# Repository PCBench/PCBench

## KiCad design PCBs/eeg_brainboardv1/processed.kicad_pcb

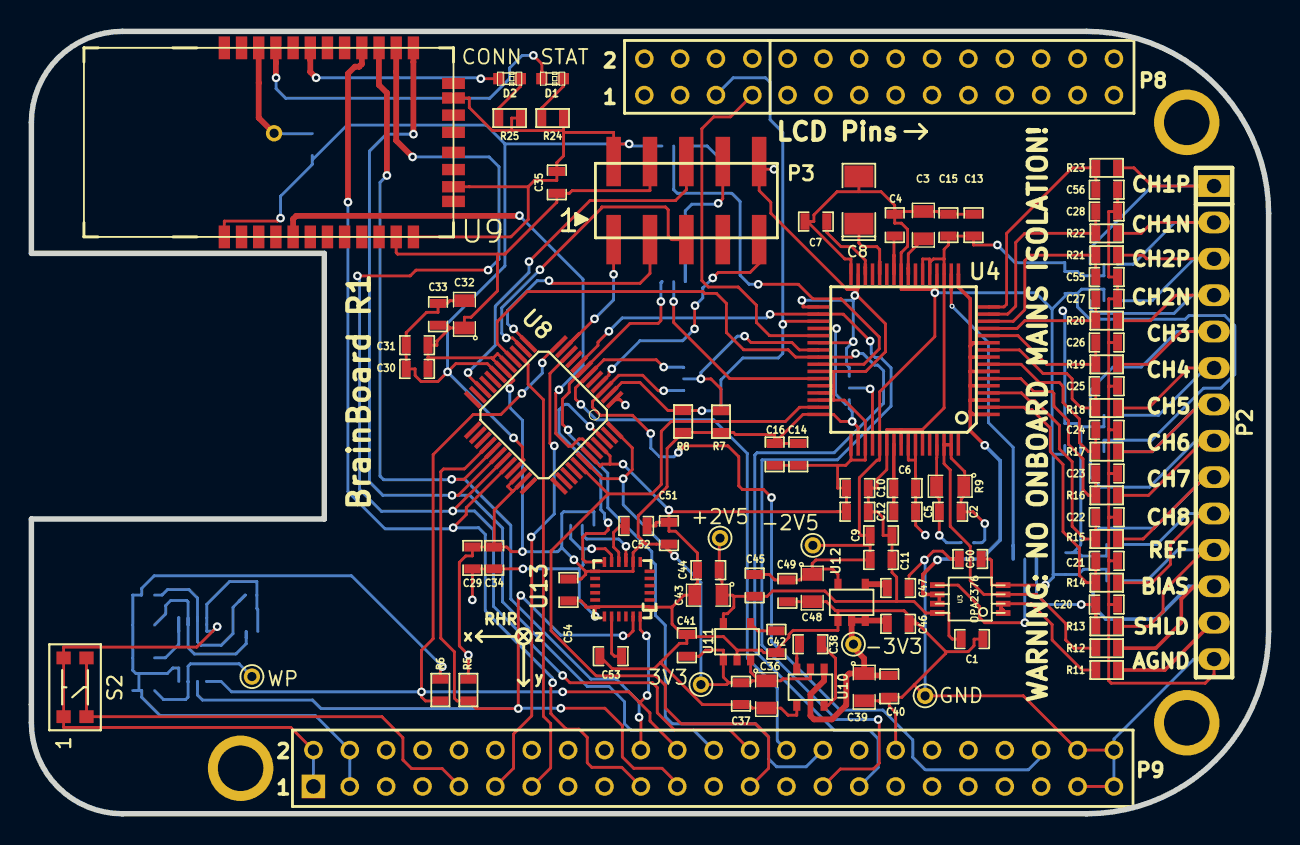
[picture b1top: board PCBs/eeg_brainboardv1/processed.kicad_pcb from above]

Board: 4 copper layers, 86.4 x 54.6 mm, 116 parts (0 on the bottom side), 86 nets.

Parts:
C1, C6, C11, C12, C15, C16, C17, C18, C19, C29, C31, C33, C34, C35, C45, C50, C51, C52: 0.1uF; SM0603_Capa
C2: 1nF; SM0603_Capa
C3, C32, C36, C39, C43, C48: 10uF; SM0805
C4, C5, C7, C9, C10, C13, C14, C37, C38, C40, C41, C46: 1uF; SM0603_Capa
C8: 100uF; SM1206POL
C20, C21, C22, C23, C24, C25, C26, C27, C28, C55, C56: 4.7nF; SM0603_Capa
C30, C44, C49: 2.2uF; SM0603_Capa
C42, C47, C54: 0.01uF; SM0603_Capa
C53: 2.2nF; SM0603_Capa
D1: STAT; LED-0603
D2: CONN; LED-0603
P1: WP; PINTST
P2: CONN_14; pin_strip_14
P3: CONN_5X2; bb02-hp10
P4: BTRST; PINTST
P5: GND; PINTST
P6: -3V3; PINTST
P7: 3V3; PINTST
P8: +2V5; PINTST
P9: -2V5; PINTST
P10: CONN_2X2; bb02-hp04
R1, R2, R3: 4.7K; SM0603
R4, R7, R8, R26: 10K; SM0603
R5, R6: 5.6K; SM0603
R9: 499K,0.1%; SM0805
R11, R12, R13, R14, R15, R16, R17, R18, R19, R20, R21, R22, R23: 4.99K; SM0603
R24, R25: 330; SM0603
S2: SMT_BUTTON; KMR231GLFS
SJ1: REF-SRB2; SparkFun-Passives-SJ_3_PASTE2&3
SJ2, SJ7: DAISY_CS; SparkFun-Passives-SJ_3_PASTE2&3
SJ3: NO BIAS FILT; SparkFun-Passives-SJ_2S-NO
SJ4: A2; SparkFun-Passives-SJ_2S-NOTRACE
SJ5: A1; SparkFun-Passives-SJ_2S-NOTRACE
SJ6: DAISY_OUT; SparkFun-Passives-SJ_3_PASTE2&3
SJ8: CLKSEL; SparkFun-Passives-SJ_3_PASTE1&2
SJ9: I2C Address Select (2&3NC); SparkFun-Passives-SJ_3_PASTE2&3
U1: 24C256; SSOP8
U2: BEAGLEBONE_BLACK; BEAGLEBONE_BLACK_EEGMOD
U3: OPA2376; msoic-8
U4: ADS1299; TQFP_64
U5, U6, U7: TPD4E001DBV; SOT23_6
U8: ATUC3L064; -TQFP48
U9: BLUETOOTH-RN42; SparkFun-RF-RN41
U10: TPS60403; SOT23-5
U11: TPS73225; SOT23-5
U12: TPS72325; SOT23-5
U13: MPU6050; QFN24-4x4

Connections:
+2.5V: C1.1, C9.1, C10.1, C11.1, C12.1, C13.1, C15.1, C17.1, C18.1, C19.1, C43.1, C44.1, C45.1, P8.1, U3.8, U4.19, U4.21, U4.22, U4.54, U4.56, U4.59, U5.5, U6.5, U7.5, U11.5
+3.3V: C14.1, C16.1, C29.1, C30.1, C31.1, C32.1, C33.1, C34.1, C35.1, C36.1, C37.1, C41.1, C51.1, C54.1, P3.4, P7.1, R1.1, R2.1, R3.1, R4.1, R5.1, R6.1, R7.1, R8.1, SJ8.1, SJ9.1, U1.8, U2.B3, U2.B4, U4.36, U4.48, U4.50, U8.17, U8.18, U8.34, U8.35, U8.42, U8.48, U9.11, U10.2, U11.1, U11.3, U13.8, U13.13
-2.5V: C3.1, C4.2, C5.2, C6.2, C7.2, C8.2, C9.2, C11.2, C13.2, C15.2, C17.2, C18.2, C19.2, C45.2, C48.1, C49.1, C50.1, P9.1, U3.4, U4.20, U4.23, U4.25, U4.32, U4.53, U4.57, U4.58, U5.2, U6.2, U7.2, U12.5
-3.3V: C39.1, C40.1, C46.1, P6.1, U10.1, U12.2, U12.3
/A0: R3.2, U1.1
/A1: R2.2, SJ5.1, U1.2
/A2: R1.2, SJ4.1, U1.3
/BrainBoard AFE//CS: R7.2, SJ2.2, U4.39
/BrainBoard AFE/BIASINV: C2.1, R9.2, SJ3.1, U4.61
/BrainBoard AFE/CLKSEL: SJ8.2, U4.52
/BrainBoard AFE/DAISY: SJ7.2, U4.41
/BrainBoard AFE/DAISY_IN: P10.1, SJ7.1
/BrainBoard AFE/DOUT: SJ6.2, U4.43
/BrainBoard AFE/SRB1: U3.6, U3.7, U4.1, U4.3, U4.5, U4.7, U4.9, U4.11, U4.17
/BrainBoard AFE/SRB2: SJ1.1, U4.18
/BrainBoard AFE/VCAP1: C8.1, U4.28
/BrainBoard AFE/VCAP2: C7.1, U4.30
/BrainBoard AFE/VCAP3: C5.1, C6.1, U4.55
/BrainBoard AFE/VCAP4: C4.1, U4.26
/BrainBoard AFE/VREFP: C3.2, U4.24
/BrainBoard Analog In/BIAS_ELEC: P2.12, R12.1, U7.3
/BrainBoard Analog In/BIAS_SHD: P2.13, R11.1
/BrainBoard Analog In/CH1ELEC_N: P2.2, R22.1, U5.6
/BrainBoard Analog In/CH1ELEC_P: P2.1, R23.1, U5.4
/BrainBoard Analog In/CH2ELEC_N: P2.4, R20.1, U5.3
/BrainBoard Analog In/CH2ELEC_P: P2.3, R21.1, U5.1
/BrainBoard Analog In/CH3ELEC_P: P2.5, R19.1, U6.4
/BrainBoard Analog In/CH4ELEC_P: P2.6, R18.1, U6.6
/BrainBoard Analog In/CH5ELEC_P: P2.7, R17.1, U6.1
/BrainBoard Analog In/CH6ELEC_P: P2.8, R16.1, U6.3
/BrainBoard Analog In/CH7ELEC_P: P2.9, R15.1, U7.4
/BrainBoard Analog In/CH8ELEC_P: P2.10, R14.1, U7.6
/BrainBoard Analog In/REF_ELEC: P2.11, R13.1, U7.1
/BrainBoard Bluetooth/FACTORY: P4.1, R26.1, U9.22
/BrainBoard Bluetooth/STATUS: D2.1, U9.19
/BrainBoard Bluetooth/STATUSn: D1.1, U9.21
/BrainBoard IMU/AD0: SJ9.2, U13.9
/BrainBoard IMU/CPOUT: C53.1, U13.20
/BrainBoard IMU/REGOUT: C52.1, U13.10
/BrainBoard MCU/RESET_MCU: P3.6, U8.22
/BrainBoard MCU/TCK: P3.1, U8.11
/BrainBoard MCU/TDI: P3.9, U8.4
/BrainBoard MCU/TDO: P3.3, U8.13
/BrainBoard MCU/TMS: P3.5, U8.14
/CS_DAISY: SJ2.1, U2.B42, U8.3
/CS_MAIN: SJ2.3, U2.B28, U8.6
/DRDY: U2.B25, U4.47, U8.41
/PWDN: R8.2, U2.A23, U4.35, U8.2
/WP: P1.1, R4.2, U1.7
AGND: C1.2, C10.2, C12.2, C14.2, C16.2, C20.2, C21.2, C22.2, C23.2, C24.2, C25.2, C26.2, C27.2, C28.2, C29.2, C30.2, C31.2, C32.2, C33.2, C34.2, C35.2, C36.2, C37.2, C39.2, C40.2, C41.2, C42.2, C43.2, C44.2, C46.2, C47.2, C48.2, C49.2, C50.2, C51.2, C52.2, C53.2, C54.2, C55.2, C56.2, P2.14, P3.2, P3.10, P5.1, R24.2, R25.2, R26.2, S2.1, S2.3, SJ4.2, SJ5.2, SJ7.3, SJ8.3, SJ9.3, U1.4, U2.B1, U2.B2, U2.B34, U2.B43, U2.B44, U2.B45, U2.B46, U4.31, U4.33, U4.38, U4.42, U4.44, U4.45, U4.46, U4.49, U4.51, U8.1, U8.19, U8.33, U8.43, U8.45, U9.1, U9.12, U9.28, U9.29, U10.4, U11.2, U12.1, U13.1, U13.11, U13.18
AIN1N: C28.1, R22.2, U4.15
AIN1P: C56.1, R23.2, U4.16
AIN2N: C27.1, R20.2, U4.13
AIN2P: C55.1, R21.2, U4.14
AIN3P: C26.1, R19.2, U4.12
AIN4P: C25.1, R18.2, U4.10
AIN5P: C24.1, R17.2, U4.8
AIN6P: C23.1, R16.2, U4.6
AIN7P: C22.1, R15.2, U4.4
AIN8P: C21.1, R14.2, U4.2
BIAS: C2.2, R9.1, R12.2, SJ3.2, U3.3, U4.62, U4.63
CLK: U2.A25, U4.37
DAISY_OUT: P3.8, SJ6.1
I2C2_SCL: R5.2, U1.6, U2.B21, U8.28, U13.23
I2C2_SDA: R6.2, U1.5, U2.B22, U8.12, U13.24
IMU_INT: U8.46, U13.12
MISO: SJ6.3, U2.B30, U8.7
MOSI: U2.B29, U4.34, U8.8
unnamed: S2.2, S2.4, U2.B9
unnamed: D2.2, R25.1
unnamed: D1.2, R24.1
unnamed: C47.1, U12.4
unnamed: C38.1, U10.5
unnamed: C38.2, U10.3
unnamed: C42.1, U11.4
unnamed: SJ1.2, U3.5
REF: C20.1, R13.2, SJ1.3
RESET_BT: U8.44, U9.5
SCLK: U2.B31, U4.40, U8.16
SHIELD: R11.2, U3.1, U3.2
UARTBT_CTS: U2.B20, U8.29, U9.15
UARTBT_RTS: U2.B19, U8.32, U9.16
UARTBT_RX: U2.B26, U8.31, U9.14
UARTBT_TX: U2.B24, U8.30, U9.13
UARTUC_RX: U2.B13, U8.15
UARTUC_TX: U2.B11, U8.10

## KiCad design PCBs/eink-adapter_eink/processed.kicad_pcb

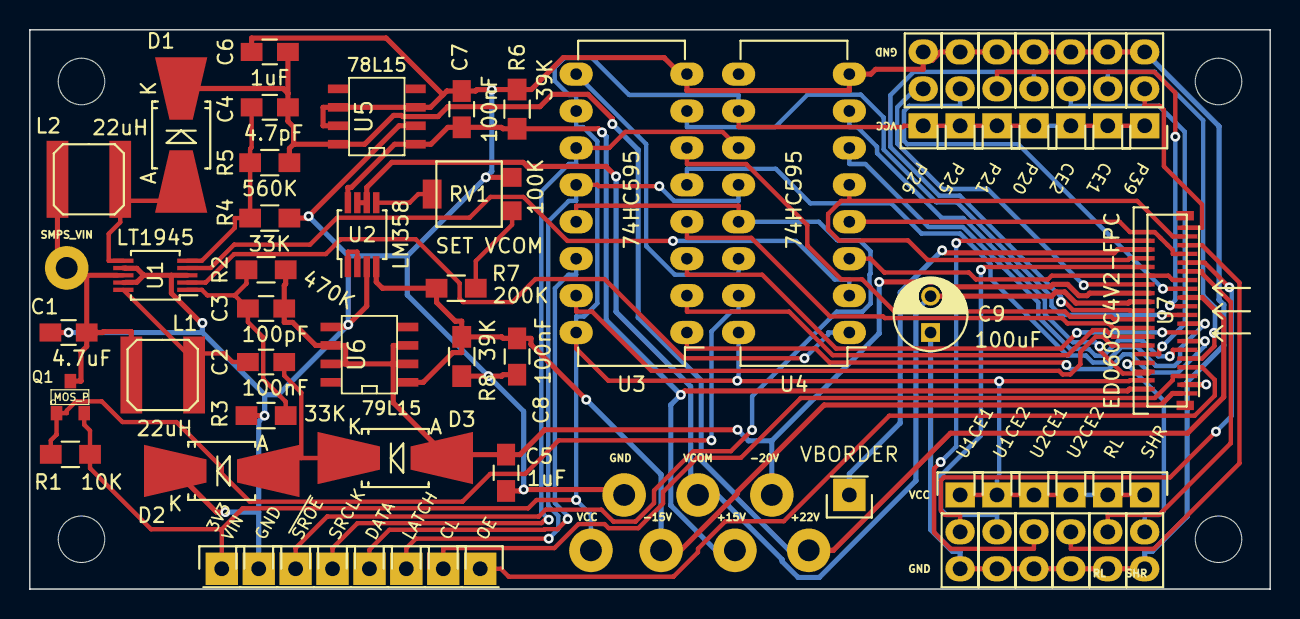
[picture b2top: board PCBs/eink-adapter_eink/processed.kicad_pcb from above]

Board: 2 copper layers, 85.3 x 38.5 mm, 65 parts (0 on the bottom side), 53 nets.

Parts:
C1: 4.7uF; C_0805_HandSoldering
C2, C7, C8: 100nF; C_0805_HandSoldering
C3: 100pF; C_0805_HandSoldering
C4: 4.7pF; C_0805_HandSoldering
C5, C6: 1uF; C_0805_HandSoldering
C9: 100uF; C_Radial_D5_L6_P2.5
D1, D2, D3: D_Schottky; SMB-SMC_Universal_Handsoldering
L1, L2: 22uH; SELF-WE-TPC_M
MNT1, MNT2, MNT3, MNT4: MountingHole_3.2mm_M3
P1, P7, P8, P9: CONN_1; Pin_Header_Straight_1x01
P2, P3, P5, P6, P10: CONN_01X01; Pin_Header_Straight_1x01
Q1: MOS_P; IRLML6402
R1: 10K; R_0805_HandSoldering
R2: 470K; R_0805_HandSoldering
R3, R4: 33K; R_0805_HandSoldering
R5: 560K; R_0805_HandSoldering
R6, R8: 39K; R_0805_HandSoldering
R7: 200K; R_0805_HandSoldering
RV1: 100K; Bourns_3314G-1
SW1, SW2, SW3, SW4, SW5, SW6, SW7, SW8, SW9, SW10, SW11, SW12, SW13: SW_SPDT_Small; Pin_Header_Straight_1x03
U1: LT1945; MSOP-10_3x3mm_Pitch0.5mm
U2: LM358; MSOP-8_3x3mm_Pitch0.65mm
U3, U4: 74HC595; DIP-16_W7.62mm_LongPads
U5: 78L15; 78LxxA
U6: 79L15; 79LxxA
U7: ED060SC4V2-FPC; FH26-39S-0.3SHW-biggerpads
W1, W2, W3, W4, W5, W6, W7, W8: TEST_1P; Measurement_Point_Round-TH_Big

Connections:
/+15V: C7.1, R6.1, U2.8, U5.VO, U7.2, W5.1
/+22V: C4.1, C6.2, D1.1, R5.2, U5.VI, U7.23, W7.1
/-15V: C8.1, R7.2, R8.1, U2.4, U6.VO, U7.1, W4.1
/-20V: C3.1, C5.1, D3.2, R2.1, U6.VI, U7.24, W8.1
/CE1: SW2.2, U7.9
/CE2: SW3.2, U7.10
/CKV: U4.4, U7.33, U7.38
/CL: P7.1, U7.5
/D0: U3.15, U7.12
/D1: U3.1, U7.13
/D2: U3.2, U7.14
/D3: U3.3, U7.15
/D4: U3.4, U7.16
/D5: U3.5, U7.17
/D6: U3.6, U7.18
/D7: U3.7, U7.19
/FB2: C4.2, R4.2, R5.1, U1.5
/GMODE: U4.3, U7.27, U7.28
/LATCH: P5.1, U3.12, U4.12
/LE: U4.7, U7.6
/NFB1: C3.2, R2.2, R3.1, U1.1
/OE: P8.1, U7.7
/P20: SW4.2, U7.20
/P21: SW5.2, U7.21
/P25: SW6.2, U7.25
/P26: SW7.2, U7.26
/P39: SW13.2, U7.39
/RL: SW8.2, U7.29
/SHR: SW1.2, U7.8
/SMPS_CTRL: Q1.G, R1.2, U4.15
/SMPS_VIN: C1.1, L1.1, L2.1, Q1.D, U1.8, W1.1
/SPH: U4.6, U7.11
/SPV: U4.5, U7.32, U7.37
/SRCLK: P3.1, U3.11, U4.11
/SRDATA: P2.1, U3.14
/SW1: C2.1, L1.2, U1.10
/SW2: D1.2, L2.2, U1.6
/U1CE1: SW10.2, U7.31
/U1CE2: SW9.2, U7.30
/U2CE1: SW12.2, U7.36
/U2CE2: SW11.2, U7.35
/VBORDER: P9.1, U7.34
/VCOM: C9.2, U2.6, U2.7, U7.22, W6.1
/VNEG_CTRL: U1.2, U4.1
/VPOS_CTRL: U1.4, U4.2
/~SROE~: P6.1, U3.13, U4.13
GND: C1.2, C5.2, C6.1, C7.2, C8.2, C9.1, D2.1, P1.1, R3.2, R4.1, R6.2, R8.2, RV1.1, SW1.3, SW2.3, SW3.3, SW4.3, SW5.3, SW6.3, SW7.3, SW8.3, SW9.3, SW10.3, SW11.3, SW12.3, SW13.3, U1.3, U1.7, U1.9, U2.3, U3.8, U4.8, U5.GND, U6.GND, U7.3, W2.1
unnamed: C2.2, D2.2, D3.1
unnamed: R7.1, RV1.3
unnamed: RV1.2, U2.5
unnamed: U2.1, U2.2
unnamed: U3.9, U4.14
VCC: P10.1, Q1.S, R1.1, SW1.1, SW2.1, SW3.1, SW4.1, SW5.1, SW6.1, SW7.1, SW8.1, SW9.1, SW10.1, SW11.1, SW12.1, SW13.1, U3.10, U3.16, U4.10, U4.16, U7.4, W3.1

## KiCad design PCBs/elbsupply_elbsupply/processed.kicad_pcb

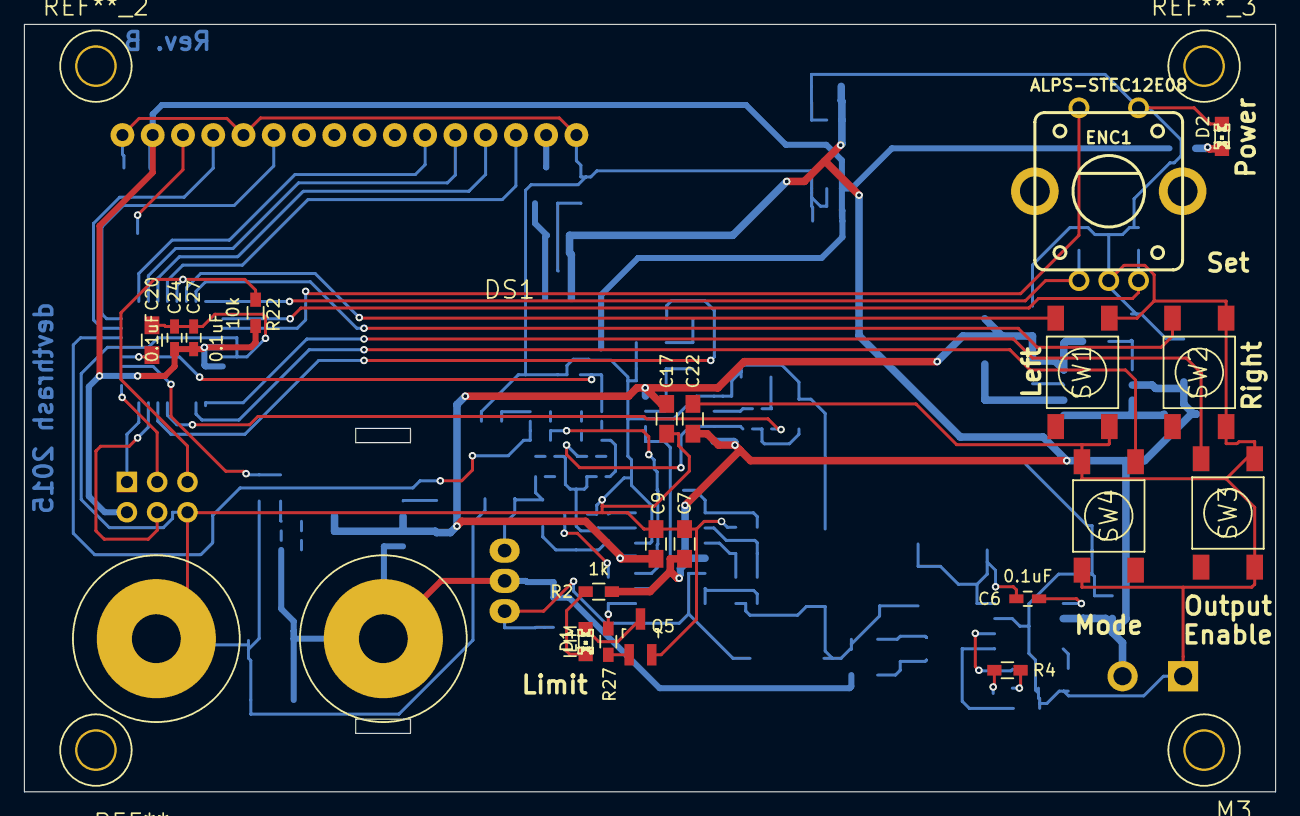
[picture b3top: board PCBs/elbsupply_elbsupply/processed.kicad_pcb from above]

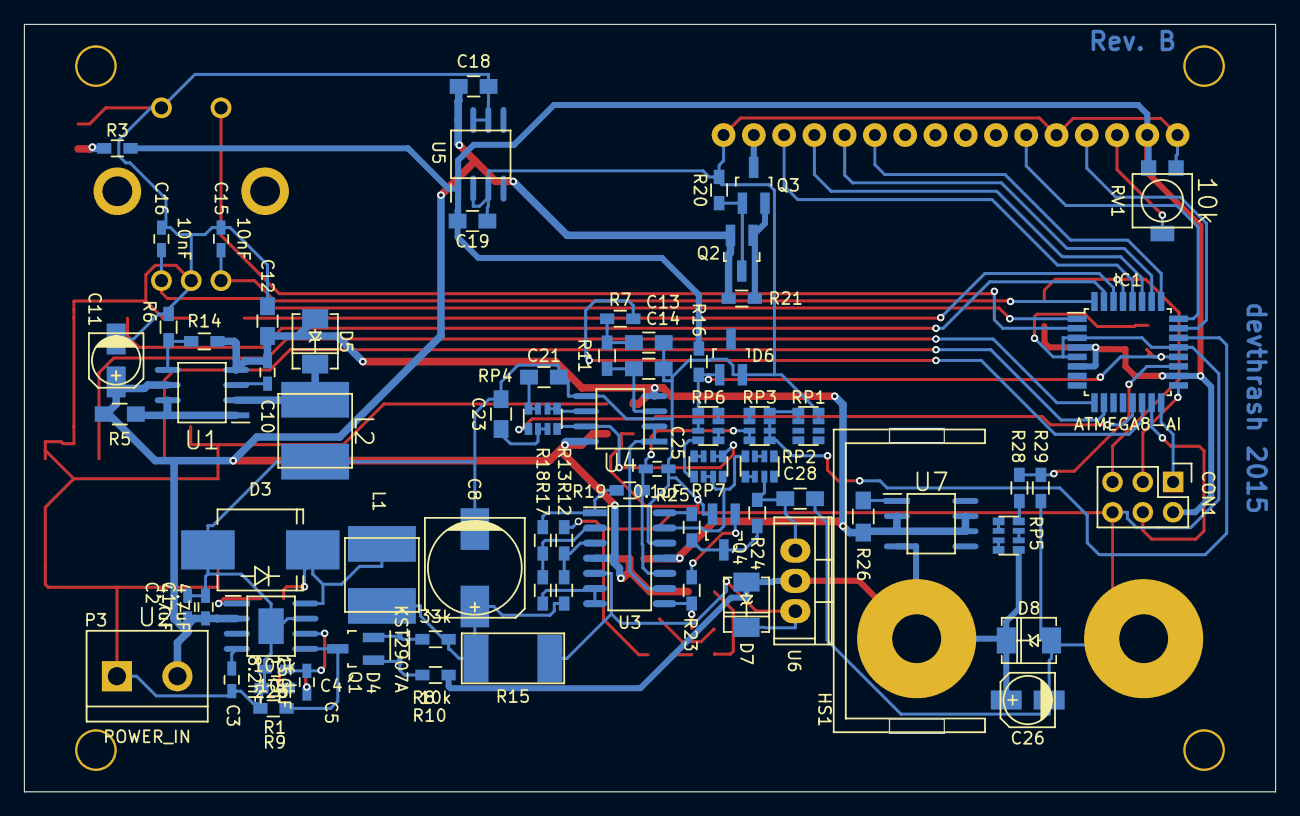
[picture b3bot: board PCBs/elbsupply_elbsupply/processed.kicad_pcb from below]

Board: 2 copper layers, 105.0 x 64.4 mm, 100 parts (76 on the bottom side), 82 nets.

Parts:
C1, C2: 4.7uF; C_0603_HandSoldering
C3: 8.2nF; C_0603_HandSoldering
C4: 22pF; C_0603_HandSoldering
C5: 150pF; C_0603_HandSoldering
C6, C24, C25, C27: 0.1uF; C_0603_HandSoldering
C7, C9, C17, C22: 0.1uF; C_0805_HandSoldering
C8: 220uF; c_elec_8x10.5
C10: 120pF; C_0603_HandSoldering
C11, C26: 10uF; c_elec_4x4.5
C12: 10uF; C_0805_HandSoldering
C13, C14, C18, C19, C20, C21, C23, C28: 1uF; C_0805_HandSoldering
C15, C16: 10nF; C_0603_HandSoldering
CON1: AVR-ISP-6; Pin_Header_Straight_2x03
D1: ILIM; LED-0805
D2: POWER; LED-0805
D3: SK54C; Diode-SMC_Handsoldering
D4: 1N4148WS; SOD-323
D5, D7, D8: SK34A; DO-214-AC_SMA
D6: LM4040; SOT-23_Handsoldering
DS1: LCD-016N002L; LCD16X2
ENC1: ALPS-STEC12E08
HS1: HEATSINK V5640A; Heatsink-V5640A
IC1: ATMEGA8-AI; TQFP-32_7x7mm_Pitch0.8mm
L1: 4,7uH; 242418FPS-Fastron
L2: 220uH; 242418FPS-Fastron
M3: Screw_PAN_Head_M3
P1: OUT_POS; SKS-PK10A
P2: OUT_GND; SKS-PK10A
P3: POWER_IN; bornier2
Q1: KST2907A; SOT23_Handsoldering
Q2: KST2907A; SOT-23_Handsoldering
Q3: IRLML6302; SOT-23_Handsoldering
Q4, Q5: 2N2222A; SOT-23_Handsoldering
R1, R13, R18: 100k; R_0603_HandSoldering
R2, R3, R20, R25: 1k; R_0603_HandSoldering
R4, R8: 33k; R_0603_HandSoldering
R5: 1R; R_0805_HandSoldering
R6: 18k; R_0603_HandSoldering
R7, R9, R10, R11, R12, R17, R19, R22, R23, R27, R28, R29: 10k; R_0603_HandSoldering
R14: 3k9; R_0603_HandSoldering
R15: 0R1; CRA2512-Bourns
R16: 220; R_0603_HandSoldering
R21: 10R; R_0603_HandSoldering
R24: 100; R_0603_HandSoldering
R26: 10R; R_0805_HandSoldering
RP1, RP2, RP3, RP4, RP5, RP6, RP7: 10k; YC164-Yageo-Handsoldering
RV1: 10k; BITech-23B
SW1: SW_L; Button-SMT-standard
SW2: SW_R; Button-SMT-standard
SW3: SW_OE; Button-SMT-standard
SW4: SW_MD; Button-SMT-standard
U1: MC34063; SO8
U2: TPS54331DDA; SO8-PowerPAD
U3: LM324; SO14
U4: LM358; SO8
U5: TS78L05CS; SO8
U6: LM350T; TO-220
U7: LM334; SO8

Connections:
+5V: C19.1, C24.2, C27.1, CON1.2, DS1.2, IC1.4, IC1.6, IC1.18, R3.1, R16.1, R22.2, RV1.1, U5.1
/2.5VREF: C20.1, D6.1, IC1.20, R16.2, RP6.1
/ENC_A: C15.1, ENC1.A, IC1.32
/ENC_B: C16.1, ENC1.B, IC1.1
/ENC_SW: ENC1.SW1, IC1.2
/ILIM: R23.1, R27.2, U3.8
/I_ADC: IC1.22, RP3.5, RP3.6, RP3.7
/I_Meas: C25.1, R19.1, RP3.3, RP3.4, U3.10
/I_PWM: IC1.14, R7.2
/I_Set: U3.9, U4.1, U4.2
/LCD_D4: DS1.11, IC1.25
/LCD_D5: DS1.12, IC1.26
/LCD_D6: DS1.13, IC1.27
/LCD_D7: DS1.14, IC1.28
/LCD_E: DS1.6, IC1.24
/LCD_RS: DS1.4, IC1.23
/LED_CC: DS1.15, Q3.3
/LED_CS: Q2.1, Q3.2, R21.2
/LIN_IN: D7.2, R15.1, U3.5, U6.3
/LIN_OUT: C26.1, D7.1, D8.2, P1.1, R10.2, RP5.1, U6.2, U7.4
/MC34_Coll: R5.1, U1.1, U1.7, U1.8
/MC34_Emit: D5.2, L2.1, U1.2
/MISO: CON1.1, IC1.16
/MOSI: CON1.4, IC1.15
/SCK: CON1.3, IC1.17
/SMPS_OUT: C8.1, L1.2, R8.1, R12.2, R15.2
/SMPS_SW: C6.2, D3.2, L1.1, U2.8
/SW_L: IC1.30, SW1.2
/SW_MD: IC1.10, SW4.2
/SW_OE: IC1.9, SW3.2
/SW_R: IC1.31, SW2.2
/V_ADC: IC1.19, R28.2, R29.2
/V_PWM: IC1.13, RP4.5
/V_Set: RP4.8, RP7.1, RP7.2, U4.7
/~RST~: CON1.5, IC1.29, R22.1
GND: C1.1, C2.1, C3.1, C4.1, C7.2, C8.2, C9.2, C11.2, C12.1, C13.2, C14.2, C15.2, C16.2, C17.2, C18.2, C19.2, C20.2, C21.2, C22.2, C23.2, C24.1, C25.2, C26.2, C27.2, C28.2, CON1.6, D2.1, D3.1, D6.2, D8.1, DS1.1, DS1.5, DS1.16, ENC1.C, ENC1.SW2, IC1.3, IC1.5, IC1.21, L2.2, P2.1, P3.1, Q4.2, Q5.2, R1.2, R6.2, R9.2, R13.1, R20.2, R29.1, RP1.3, RP1.4, RV1.3, SW1.1, SW2.1, SW3.1, SW4.1, U2.7, U2.9, U3.12, U4.5, U5.2, U5.3, U5.6, U5.7
unnamed: C3.2, U2.4
unnamed: C4.2, C5.1, U2.6
unnamed: C5.2, R4.1
unnamed: C6.1, U2.1
unnamed: C10.1, U1.3
unnamed: C13.1, R7.1, R11.2
unnamed: C14.1, R11.1, U4.3
unnamed: C21.1, RP4.3, RP4.4
unnamed: C23.1, RP4.6, RP4.7
unnamed: C28.1, R24.1, RP2.7, U6.1
unnamed: D1.1, Q5.3
unnamed: D1.2, R2.2
unnamed: D2.2, R3.2
unnamed: D4.1, Q1.1, R10.1
unnamed: D4.2, Q1.2, R8.2
unnamed: DS1.3, RV1.2
unnamed: Q1.3, R9.1, U2.5
unnamed: Q2.3, Q3.1, R20.1
unnamed: Q4.1, R23.2
unnamed: Q4.3, R24.2, R25.1
unnamed: Q5.1, R27.1
unnamed: R1.1, R4.2
unnamed: R12.1, R13.2, U3.3
unnamed: R6.1, R14.2, U1.5
unnamed: R17.1, U3.6, U3.7
unnamed: R17.2, R18.2, U3.2
unnamed: R18.1, R19.2, U3.1
unnamed: R25.2, U3.14
unnamed: R26.1, U7.1
unnamed: R28.1, RP5.4
unnamed: RP1.5, RP1.6, RP3.8
unnamed: RP2.2, RP2.3
unnamed: RP2.4, RP7.6, RP7.7, U3.13
unnamed: RP2.5, RP2.6
unnamed: RP3.1, RP3.2
unnamed: RP4.1, RP4.2, U4.6
unnamed: RP5.2, RP5.3
unnamed: RP5.5, RP5.6
unnamed: RP5.7, RP5.8
unnamed: RP6.2, RP6.3
unnamed: RP6.4, RP7.5
unnamed: RP6.5, RP6.6
unnamed: RP6.7, RP6.8
unnamed: RP7.3, RP7.4
VCC: C1.2, C2.2, C7.1, C11.1, C18.1, C22.1, P3.2, Q2.2, R2.1, R5.2, R21.1, U1.6, U2.2, U3.4, U4.8, U5.8
VEE: C9.1, C10.2, C12.2, C17.1, D5.1, R14.1, R26.2, U1.4, U3.11, U4.4, U7.2, U7.3, U7.6, U7.7

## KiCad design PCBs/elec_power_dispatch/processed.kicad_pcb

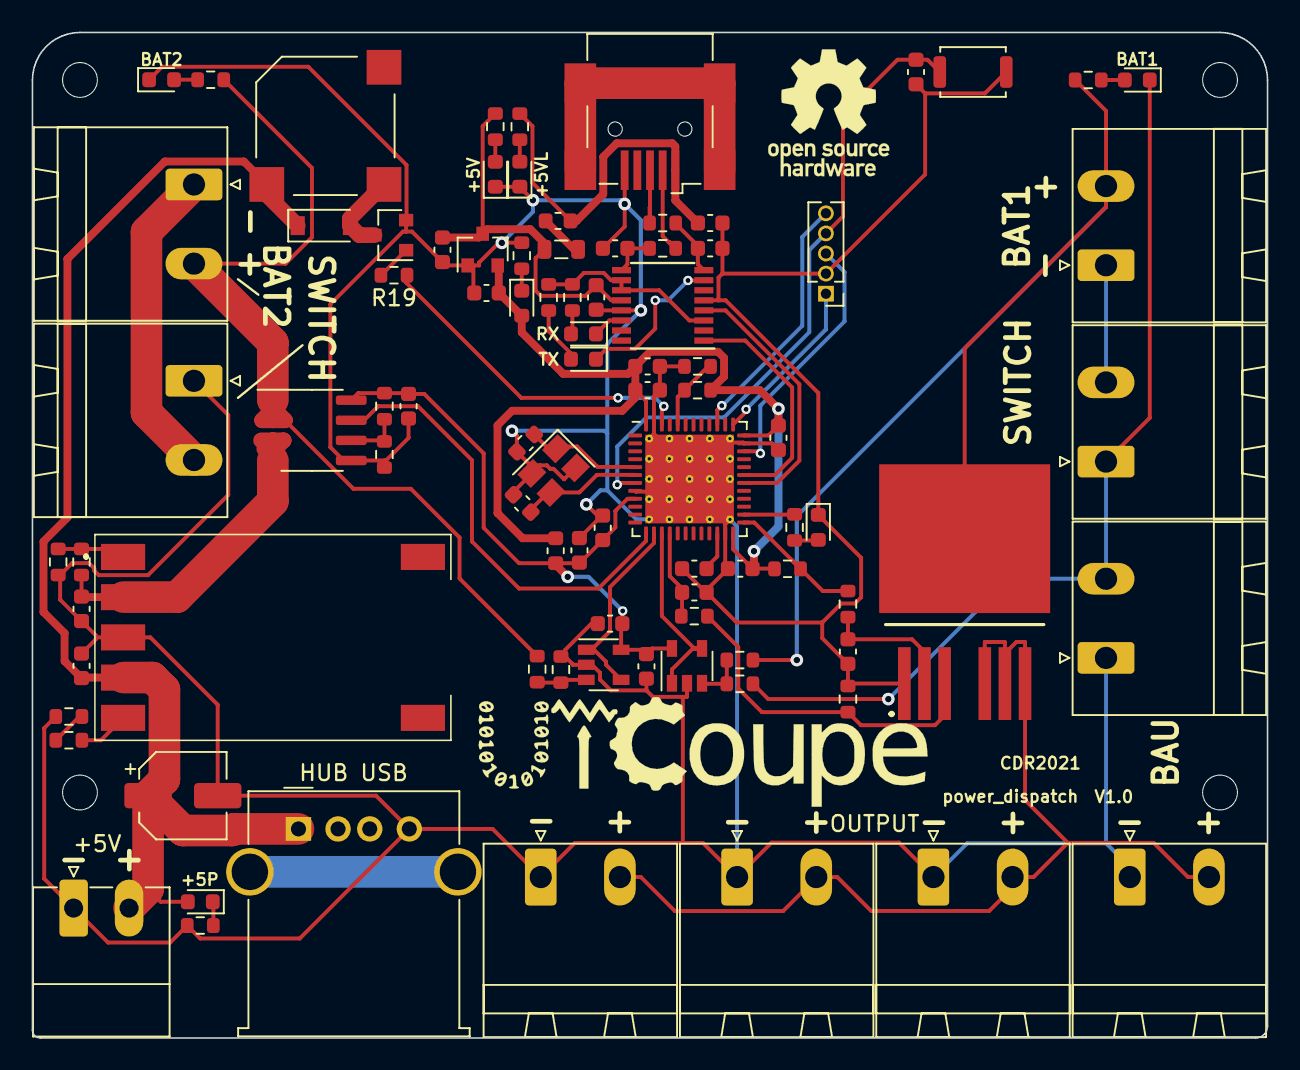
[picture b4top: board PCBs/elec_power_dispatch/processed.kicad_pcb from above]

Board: 2 copper layers, 78.0 x 63.5 mm, 95 parts (0 on the bottom side), 57 nets.

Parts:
BZ1: MLT-8530; MagneticBuzzer_Kobitone_254-EMB84Q-RO
C1, C4, C9, C13, C14, C15, C17, C18, C22, C24, C26: 100nF; C_0603_1608Metric
C2: 100uF/10V; CP_Elec_5x5.4
C3, C6, C12: 4u7; C_0603_1608Metric
C5, C7: 10uF; C_0603_1608Metric
C8: 220nF; C_0603_1608Metric
C10, C11: 12pF; C_0603_1608Metric
C16: 1u; C_0603_1608Metric
C19: 10nF; C_0603_1608Metric
C23, C25: 47pF; C_0603_1608Metric
D1, D2, D3, D4, D7, D9: red0603; LED_0603_1608Metric
D5, D6: blue0603; LED_0603_1608Metric
D8: 1N4148W; D_SOD-123
D10: green0603; LED_0603_1608Metric
F1: 100mA; Fuse_0603_1608Metric
FB1: 100 @ 100MHz; L_0805_2012Metric
H1, H2, H3, H4: MountingHole; MountingHole_2.2mm_M2
IC1: SRBH-06H1A1G; SRBH06H1A1G
IC2: BTS500251TADATMA2; IPB180N03S4L01
J1, J2, J3, J4, J5, J8, J9, J10, J11: Conn_01x02; PhoenixContact_MSTBA_2,5_2-G_1x02_P5.00mm_Horizontal
J6: USB_B_Mini; USB_Mini-B_Wuerth_65100516121_Horizontal
J7: Conn_01x05; PinHeader_1x05_P1.27mm_Vertical
J13: Conn_01x02; PhoenixContact_MC_1,5_2-G-3.5_1x02_P3.50mm_Horizontal
J15: USB_A; USB_A_Molex_67643_Horizontal
L1: 39nH; L_0603_1608Metric
LOGO1: Logo_Open_Hardware_Large; OSHW-Logo_7.5x8mm_SilkScreen
Q1: 2N7002E; SOT-23
R1, R10, R14, R24, R26: 3K3; R_0603_1608Metric
R2, R12: 4K7; R_0603_1608Metric
R3, R5, R6, R8, R25, R27, R28: 10K; R_0603_1608Metric
R4: 2K2; R_0603_1608Metric
R7, R9: 1K5; R_0603_1608Metric
R11, R13: 1K; R_0603_1608Metric
R15, R16: 27R; R_0603_1608Metric
R17, R20, R21: NC; R_0603_1608Metric
R18: 0R; R_0603_1608Metric
R19: 470R; R_0603_1608Metric
R22, R23: 270R; R_0603_1608Metric
SW1: SKRKAEE020; SW_Push_SPST_NO_Alps_SKRK
U1, U8: MCP6L01x-xOT; SOT-23-5
U2: STM32F411CEUx; QFN-48-1EP_7x7mm_P0.5mm_EP5.6x5.6mm_ThermalVias
U3: FT230XS; SSOP-16_3.9x4.9mm_P0.635mm
U4: ACS722xLCTR-10AB; SOIC-8_3.9x4.9mm_P1.27mm
U5: XC6206P332MR; SOT-23
Y1: 1C208000BC0K 8MHz; Crystal_SMD_3225-4Pin_3.2x2.5mm

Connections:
+3.3VA: C4.1, C9.1, C16.2, C17.2, C18.1, L1.2, R17.1, U1.5, U2.9, U4.8, U8.5
+3V3: C7.1, C12.2, C13.2, C14.2, C22.2, D7.2, L1.1, R20.2, R21.1, U2.24, U2.36, U2.48, U5.2
+5V: C5.1, C24.1, FB1.1, R24.1, U3.12, U5.3
+5VL: C3.1, F1.2, J6.1, R1.1
+5VP: BZ1.1, C2.1, C26.1, D3.2, D8.1, IC1.4, J13.2, J15.1
+12P: IC2.5, IC2.6, IC2.7, J8.2, J9.2, J10.2, J11.2
+12V: C1.1, IC1.2, R27.1, U4.3, U4.4
+12VA: J1.2, R3.1, R6.1, U4.1, U4.2
+BATT: IC2.4, J3.2, R5.1, R8.1
/TRIM: IC1.5, R10.2
BOOT0: R20.1, R25.2, U2.44
BUZZER: R19.1, U2.46
CBUS1: D5.1, U3.14
CBUS2: D6.1, U3.7
GND: C1.2, C2.2, C3.2, C4.2, C5.2, C6.2, C7.2, C8.2, C9.2, C10.1, C11.2, C12.1, C13.1, C14.1, C15.2, C16.1, C17.1, C18.2, C19.2, C22.1, C23.2, C24.2, C25.2, C26.2, D1.1, D2.1, D9.1, D10.1, IC1.3, IC2.1, J2.1, J5.1, J6.5, J7.2, J8.1, J9.1, J10.1, J11.1, J13.1, J15.4, Q1.2, R4.1, R7.2, R11.1, R13.1, R14.2, R18.2, R25.1, R28.2, SW1.2, U1.2, U2.8, U2.23, U2.35, U2.47, U2.49, U3.5, U3.13, U4.5, U5.1, U8.2, Y1.2, Y1.4
GNDBATT: J3.1, J4.2
HSE_IN: C10.2, U2.5, Y1.1
HSE_OUT: C11.1, U2.6, Y1.3
LED0: R26.1, U2.26
NRST: C15.1, J7.4, SW1.1, U2.7
unnamed: BZ1.2, D8.2, Q1.3
unnamed: C6.1, U2.22
unnamed: C8.1, IC2.2, R12.1
unnamed: C23.1, R15.2, U3.9
unnamed: C25.1, R16.2, U3.8
unnamed: D1.2, R1.2
unnamed: D2.2, R3.2
unnamed: D3.1, R4.2
unnamed: D4.1, J4.1, J5.2, R9.2
unnamed: D4.2, R5.2
unnamed: D5.2, R22.1
unnamed: D6.2, R23.1
unnamed: D7.1, R14.1
unnamed: D9.2, R24.2
unnamed: D10.2, R26.2
unnamed: F1.1, FB1.2
unnamed: IC1.1, R27.2, R28.1
unnamed: IC2.3, R2.1, R13.2
unnamed: J1.1, J2.2
unnamed: Q1.1, R19.2
unnamed: R6.2, R7.1, U1.3
unnamed: R8.2, R9.1, U8.3
unnamed: R10.1, R11.2
unnamed: R17.2, R18.1, U4.6
PWRCMD: R12.2, R21.2, U2.25
SWCLK: J7.1, U2.37
SWDIO: J7.3, U2.34
SWO: J7.5, U2.39
UART_RX: U2.31, U3.1
UART_TX: U2.30, U3.4
USB_D+: J6.3, R16.1
USB_D-: J6.2, R15.1
VCCIO: R22.2, R23.2, U3.3, U3.10, U3.11
VILOGIC: U2.13, U4.7
VIPOWER: C19.1, R2.2, U2.16
VVLOGIC: U1.1, U1.4, U2.14
VVPOWER: U2.15, U8.1, U8.4

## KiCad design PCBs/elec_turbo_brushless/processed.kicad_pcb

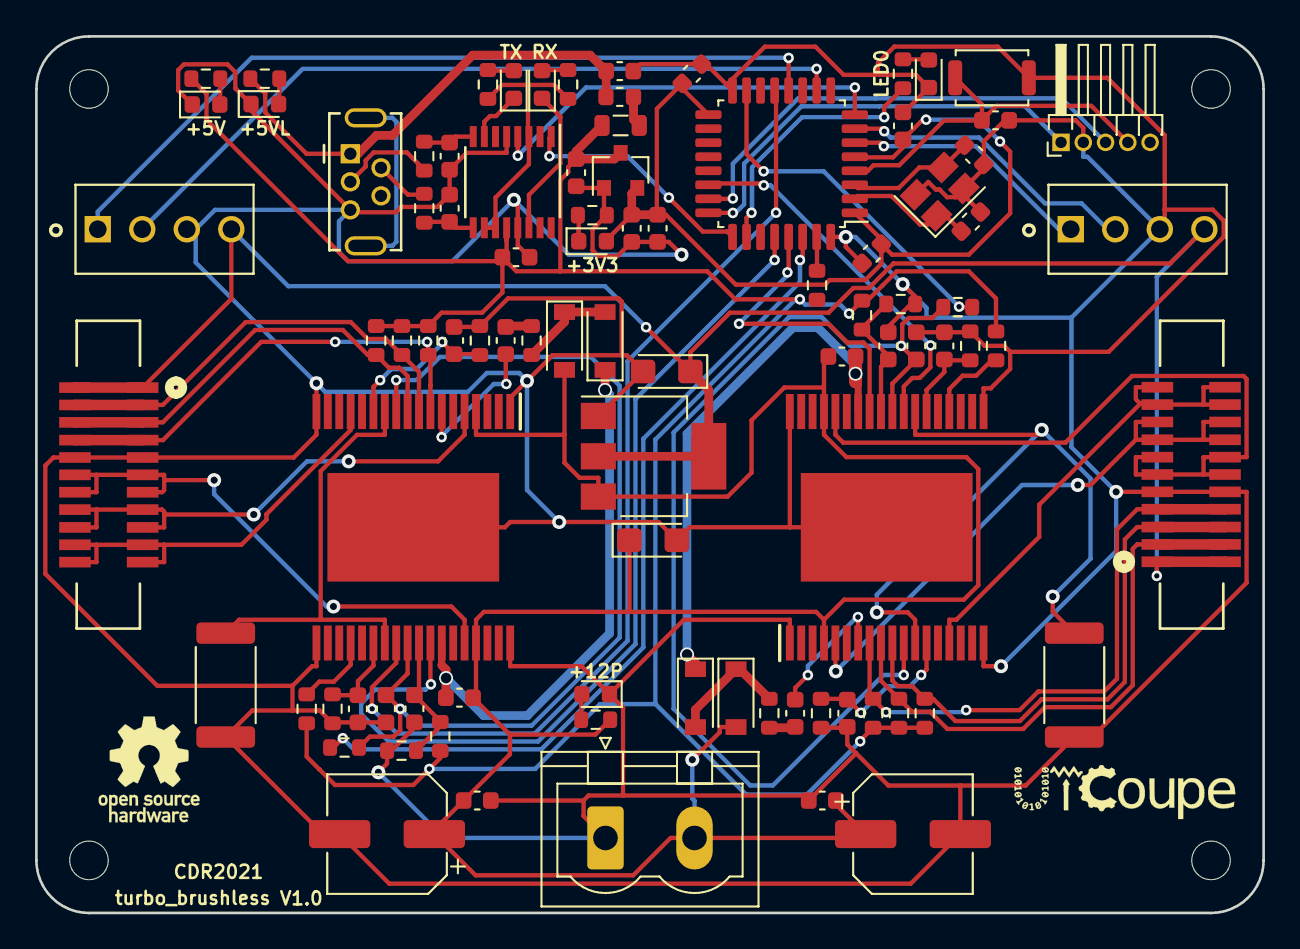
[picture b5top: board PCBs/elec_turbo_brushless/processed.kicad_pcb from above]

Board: 2 copper layers, 70.0 x 50.0 mm, 96 parts (0 on the bottom side), 72 nets.

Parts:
C1, C11: 4u7; C_0603_1608Metric
C2, C5: 10uF; C_0603_1608Metric
C3, C4: 12pF; C_0603_1608Metric
C6: 10uF; CP_EIA-3216-18_Kemet-A
C7: 22uF; CP_EIA-3216-18_Kemet-A
C8, C10: 47pF; C_0603_1608Metric
C9, C12, C13, C18, C22, C25, C31: 100nF; C_0603_1608Metric
C14, C26: 220nF; C_0603_1608Metric
C15, C19, C28, C29: 10nF; C_0603_1608Metric
C16, C23: 1nF; C_0603_1608Metric
C17, C24: 100uF; CP_Elec_6.3x7.7
C20, C30: 5.6nF; C_0603_1608Metric
C21, C27: 47nF; C_0603_1608Metric
D1, D2, D5, D11: red0603; LED_0603_1608Metric
D3, D4: blue0603; LED_0603_1608Metric
D6, D7, D9, D10: 1N4148; D_SOD-123
D8: green0603; LED_0603_1608Metric
F1: 100mA; Fuse_0603_1608Metric
FB1: 100 @ 100MHz; L_0805_2012Metric
H1, H2, H3, H4: MountingHole; MountingHole_2.2mm_M2
IC1, IC2: L6235PD; SOP65P1420X360-37N
J1: USB_B_Mini; USB_Mini-B_Tensility_54-00023_Vertical
J2: Conn_01x02; PhoenixContact_MSTBVA_2,5_2-G-5,08_1x02_P5.08mm_Vertical
J3, J5: Conn_01x11; MOLEX_52610-0571_FPC_01x11_p1.0mm
J4: Conn_01x05; PinHeader_1x05_P1.27mm_Horizontal
J6, J7: Conn_01x04; Headers-Wire_Housings_HEADER_4POS_HE14
LOGO1: Logo_Open_Hardware_Large; OSHW-Logo_5.7x6mm_SilkScreen
R1, R2, R3, R8: 3K3; R_0603_1608Metric
R4, R5: 27R; R_0603_1608Metric
R6, R7: 270R; R_0603_1608Metric
R9, R11, R12, R13, R18, R20, R21, R22, R24, R28, R31, R32: 10K; R_0603_1608Metric
R10, R27: 100; R_0603_1608Metric
R14, R23: 33K; R_0603_1608Metric
R15, R26: 47K; R_0603_1608Metric
R16, R30: 100K; R_0603_1608Metric
R17, R25: N/A; R_0603_1608Metric
R19, R29: 0.25/1W 1%; R_2512_6332Metric
SW1: SKRKAEE020; SW_Push_SPST_NO_Alps_SKRK
U1: STM32F303K8Tx; LQFP-32_7x7mm_P0.8mm
U2: XC6206P332MR; SOT-23
U3: FT230XS; SSOP-16_3.9x4.9mm_P0.635mm
U4: AMS1117-5.0; SOT-223-3_TabPin2
Y1: 1C208000BC0K 8MHz; Crystal_SMD_3225-4Pin_3.2x2.5mm

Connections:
+3V3: C5.1, C11.1, C12.1, C13.1, C31.1, D2.2, U1.1, U1.5, U1.17, U2.2
+5V: C2.1, C9.1, FB1.1, R8.1, R9.1, R11.2, R12.2, R13.2, R18.1, R20.2, R21.2, R22.2, R24.1, R28.1, U2.3, U3.12
+5VL: C1.1, F1.2, J1.1, R1.1
+5VP: C7.1, J3.1, J5.1, J6.4, J7.4, U4.2
+12P: C6.1, C14.1, C17.1, C18.1, C24.1, C25.1, C26.1, D6.2, D9.2, IC1.4, IC1.33, IC2.4, IC2.33, J2.2, R32.1, U4.3
/DIAG_1: C20.1, IC1.11, IC1.27, R16.1
/DIAG_2: C30.1, IC2.11, IC2.27, R30.1
/VBOOT_1: C14.2, D7.1, IC1.30
/VBOOT_2: C26.2, D10.1, IC2.30
/VCP_1: C15.1, IC1.7
/VCP_2: C29.1, IC2.7
BOOT0: R31.1, U1.31
BRAKE_1: IC1.29, U1.28
BRAKE_2: IC2.29, U1.29
CBUS1: D3.1, U3.14
CBUS2: D4.1, U3.7
ENABLE_1: R16.2, U1.30
ENABLE_2: R30.2, U1.15
ENC_A_1: J7.1, U1.12
ENC_A_2: J6.1, U1.6
ENC_B_1: J7.2, U1.10
ENC_B_2: J6.2, U1.7
FWD_REV_1: IC1.26, U1.13
FWD_REV_2: IC2.26, U1.22
GND: C1.2, C2.2, C3.2, C4.2, C5.2, C6.2, C7.2, C8.2, C9.2, C10.2, C11.2, C12.2, C13.2, C16.1, C17.2, C18.2, C19.1, C20.2, C21.2, C22.2, C23.1, C24.2, C25.2, C27.2, C28.1, C30.2, C31.2, D1.1, D5.1, D8.1, D11.1, IC1.1, IC1.18, IC1.19, IC1.36, IC1.37, IC2.1, IC2.18, IC2.19, IC2.36, IC2.37, J1.5, J2.1, J3.5, J4.2, J5.5, J6.3, J7.3, R3.2, R14.2, R15.2, R17.2, R19.2, R23.2, R25.2, R26.2, R29.2, SW1.2, U1.16, U1.32, U2.1, U3.5, U3.13, U4.1, Y1.2, Y1.4
H1_1: IC1.10, J3.3, R13.1
H1_2: IC2.10, J5.3, R22.1
H2_1: IC1.8, J3.4, R11.1
H2_2: IC2.8, J5.4, R20.1
H3_1: IC1.9, J3.2, R12.1
H3_2: IC2.9, J5.2, R21.1
HSE_IN: C3.1, U1.2, Y1.1
HSE_OUT: C4.1, U1.3, Y1.3
LED0: R2.1, U1.26
NRST: C22.1, J4.4, SW1.1, U1.4
unnamed: C8.1, R4.2, U3.9
unnamed: C10.1, R5.2, U3.8
unnamed: C15.2, R10.1
unnamed: C16.2, IC1.13, R14.1
unnamed: C19.2, IC1.24, R15.1
unnamed: C21.1, IC1.28, R9.2, R17.1
unnamed: C23.2, IC2.13, R23.1
unnamed: C27.1, IC2.28, R24.2, R25.1
unnamed: C28.2, IC2.24, R26.1
unnamed: C29.2, R27.1
unnamed: D1.2, R1.2
unnamed: D2.1, R3.1
unnamed: D3.2, R6.1
unnamed: D4.2, R7.1
unnamed: D5.2, R8.2
unnamed: D6.1, D7.2, R10.2
unnamed: D8.2, R2.2
unnamed: D9.1, D10.2, R27.2
unnamed: D11.2, R32.2
unnamed: F1.1, FB1.2
OUT1_1: IC1.15, J3.10, J3.11
OUT1_2: IC2.15, J5.10, J5.11
OUT2_1: IC1.5, J3.8, J3.9
OUT2_2: IC2.5, J5.8, J5.9
OUT3_1: IC1.32, J3.6, J3.7
OUT3_2: IC2.32, J5.6, J5.7
SENSE_1: IC1.12, IC1.25, R19.1
SENSE_2: IC2.12, IC2.25, R29.1
SWCLK: J4.1, U1.24
SWDIO: J4.3, U1.23
TACHO_1: IC1.22, R18.2
TACHO_2: IC2.22, R28.2
UART_RX: U1.25, U3.1
UART_TX: U1.8, U3.4
USB_D+: J1.3, R5.1
USB_D-: J1.2, R4.1
VCCIO: R6.2, R7.2, U3.3, U3.10, U3.11

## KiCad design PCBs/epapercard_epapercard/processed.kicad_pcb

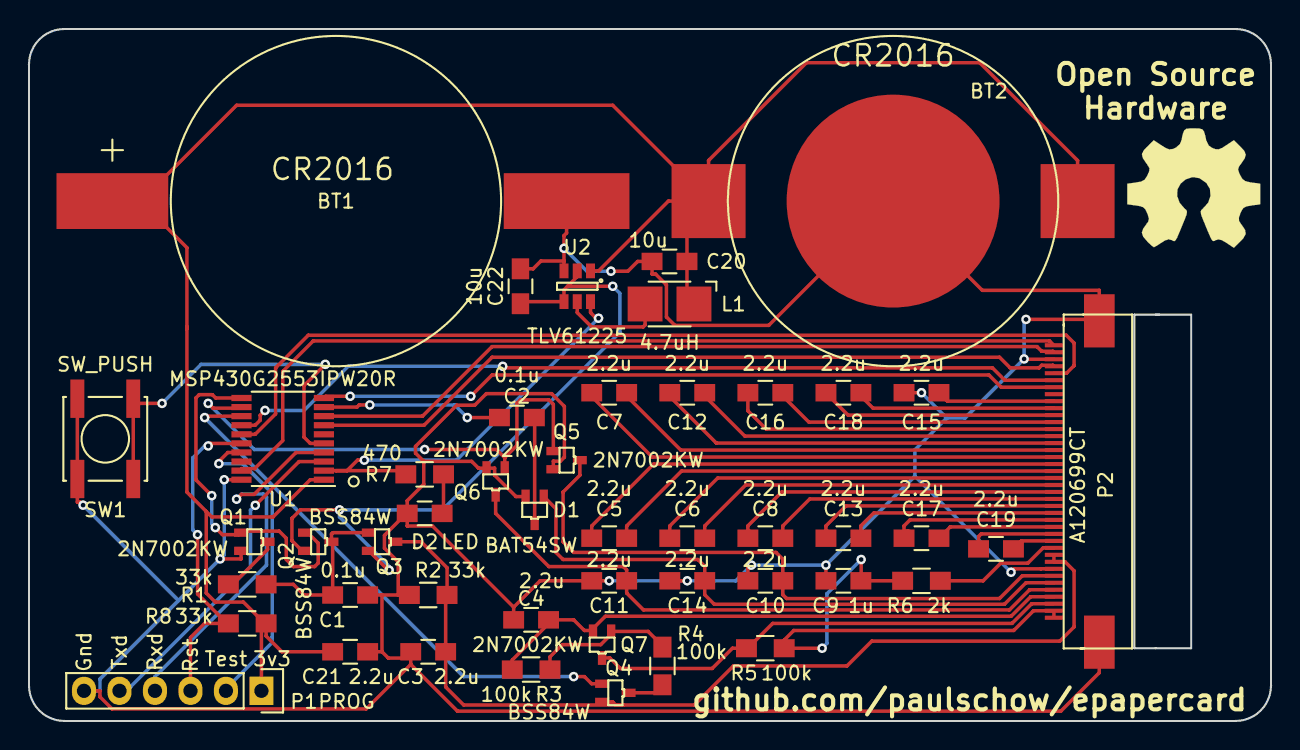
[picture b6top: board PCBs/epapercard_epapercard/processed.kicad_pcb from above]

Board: 2 copper layers, 88.9 x 49.5 mm, 47 parts (0 on the bottom side), 55 nets.

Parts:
BT1: CR2016; CR2016sm-F2N
BT2: CR2016; CR2032sm
C1, C2: 0.1u; C_0805_HandSoldering
C3, C4, C5, C6, C7, C8, C10, C11, C12, C13, C14, C15, C16, C17, C18, C19, C21: 2.2u; C_0805_HandSoldering
C9: 1u; C_0805_HandSoldering
C20, C22: 10u; C_0805_HandSoldering
D1: BAT54SW; SOT-323
D2: LED; C_0805_HandSoldering
L1: 4.7uH; Inductor_1212
P1: PROG; Pin_Header_Straight_1x06
P2: A120699CT
Q1, Q5, Q6, Q7: 2N7002KW; SOT-323
Q2, Q3, Q4: BSS84W; SOT-323
R1, R2, R8: 33k; R_0805_HandSoldering
R3, R4, R5: 100k; R_0805_HandSoldering
R6: 2k; R_0805_HandSoldering
R7: 470; R_0805_HandSoldering
SW1: SW_PUSH; SW_SPST_EVPBF
U1: MSP430G2553IPW20R; TSSOP-20_4.4x6.5mm_Pitch0.65mm
U2: TLV61225; SOT-23-6

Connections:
+3.3VP: C3.2, P2.31, P2.32, Q3.3, Q4.2, R2.2
+3V3: BT1.1, BT2.1, C20.2, C21.2, L1.1, P1.1, R8.2, U1.1, U2.1
/BORDER: P2.38, Q7.3, R5.2
/EPD_CS: P2.1, U1.19
/RESET: P2.7, U1.10
/VCOM: C9.1, P2.39, P2.40, R5.1, R6.2
/VDH: C11.1, P2.36, Q6.3
/VDL: C4.1, P2.37, Q7.2, R3.2
/VGH: C10.1, P2.34, Q5.3
/VGL: C14.1, D1.1, P2.35
/Vboost: C22.2, Q2.2, Q3.2, U2.2, U2.4
/button: SW1.1, U1.5
/led: R7.2, U1.2, U2.6
/rst: P1.3, R8.1, U1.16
/rxd: P1.4, U1.4
/test: P1.2, U1.17
/txd: P1.5, U1.3
BORDER_CONTROL: Q4.1, U1.13
BUSY: P2.2, U1.8
DISCHARGE: Q5.1, Q6.1, U1.12
GND: BT1.2, BT2.2, C1.1, C3.1, C4.2, C9.2, C10.2, C11.2, C14.2, C15.2, C20.1, C21.1, C22.1, D1.2, D2.1, P1.6, P2.3, P2.33, P2.41, Q1.2, Q5.2, Q6.2, R2.1, SW1.2, U1.20, U2.3
unnamed: C1.2, Q2.3, Q3.1, R1.1
unnamed: C2.1, D1.3
unnamed: C5.1, P2.18
unnamed: C5.2, P2.19
unnamed: C6.1, P2.20
unnamed: C6.2, P2.21
unnamed: C7.1, P2.16
unnamed: C7.2, P2.17
unnamed: C8.1, P2.22
unnamed: C8.2, P2.23
unnamed: C12.1, P2.14
unnamed: C12.2, P2.15
unnamed: C13.1, P2.24
unnamed: C13.2, P2.25
unnamed: C15.1, P2.9
unnamed: C16.1, P2.12
unnamed: C16.2, P2.13
unnamed: C17.1, P2.26
unnamed: C17.2, P2.27
unnamed: C18.1, P2.10
unnamed: C18.2, P2.11
unnamed: C19.1, P2.28
unnamed: C19.2, P2.29
unnamed: D2.2, R7.1
unnamed: L1.2, U2.5
unnamed: P2.30, R6.1
unnamed: Q1.3, R1.2
unnamed: Q4.3, R4.1
unnamed: Q7.1, R3.1, R4.2
PANEL_ON: Q1.1, Q2.1, U1.11
PWM: C2.2, U1.9
SPI_CLK: P2.4, U1.7
SPI_MISO: P2.6, U1.14
SPI_MOSI: P2.5, U1.15
